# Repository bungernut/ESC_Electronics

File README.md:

# Board
Order the board at oshpark https://oshpark.com/shared_projects/LPLUU39w

# ESC_Electronics
Digikey: https://www.digikey.com/short/nt3pmbw5

|Reference(s)|Value|Digikey|
|-|-|-|
| BT1, BT2, BT3, BT4, BT5, BT6 | 12V | BH23APC-ND |
| C1, C4 | 10uF | 1276-1096-1-ND |
| C2 | open |  |
| C3, C7 | 1nF | 399-CGP1C102KNYDAAWL25-ND |
| C5 | 1pF | 445-180733-1-ND |
| C6 | 4700pF | 399-CGP1C472MNWDAAWL25-ND |
| C8 | open |  |
| C9, C10, C15, C16 | 0.1uF | 1276-1003-1-ND |
| C11, C12 | 330uF | 1189-1766-ND |
| C13, C14 | 0.33uF | 1276-2926-1-ND |
| D1, D2 | RB751V-40 | MBR0540TPMSCT-ND |
| F1, F2 | Polyfuse_Small | 507-1794-1-ND |
| FB1, FB2 | FerriteBead_Small | 732-6715-1-ND |
| H1, H2, H3, H4 | MountingHole |  |
| H5 | DiodeFeedThru |  |
| H6, H7 | MountingHole |  |
| J1 | Batt probe | N/A |
| J2 | CA probe | N/A |
| J3 | Test Input BNC | ARF2005-ND |
| J4 | -1000VDC SHV | 4912-SHV-BR-ND |
| J5 | RV Prob |  |
| J6 | Output BNC | ARF2005-ND |
| J7 | DC Power | WM4825-ND |
| J8 | -8V |  |
| J9 | +8V |  |
| R1 | open |  |
| R2, R3, R5 | 10M | HVA12FA10M0CT-ND |
| R4 | 100M | HVA12FA100MCT-ND |
| R6 | 47 | RPC0805JT47R0 |
| R7 | open |  |
| R8 | 0 | RMCF0805ZT0R00 |
| R9 | 750 | RMCF0805FT750RCT-ND |
| R10 | 20k | RMCF0805FT20K0CT-ND |
| RV1 | 10k | 3266W-103LF-ND |
| U1 | CR110 | ED11161-ND |
| U2 | SiPhotodiode |  |
| U3 | TL051CP | 296-7192-5-ND |
| U4 | UA78M08 | 296-12612-1-ND |
| U5 | UA79M08 | 296-19678-1-ND |

Other items for assembly:
| Part | Ref | Link |
|-|-|-|
| Cremat CR110 | U1 | https://www.cremat.com/home/charge-sensitive-preamplifiers/ |
| SiDiode | U2 | https://www.hamamatsu.com/us/en/product/optical-sensors/photodiodes/si-photodiodes/S3204-09.html |
| 8 PDIP Socket | U3 |  https://www.digikey.com/en/products/detail/te-connectivity-amp-connectors/1-2199298-2/5022039 |
| Red HV Hookup Wire | | https://www.digikey.com/en/products/detail/cnc-tech/3239-24-1-0500-004-1-TS/5968804 |
| BLK HV Hookup Wire | | https://www.digikey.com/en/products/detail/cnc-tech/3239-24-1-0500-001-1-TS/5968800 |
| Electronic Box | | https://www.digikey.com/en/products/detail/bud-industries/CN-5709/1219181 |
| SHV Bulkhead | | https://www.digikey.com/en/products/detail/te-connectivity-amp-connectors/51494-2/298100 |
| Power Cable Assembly | | https://www.digikey.com/en/products/detail/te-connectivity-amp-connectors/2273001-1/5167970 |
| Power Cable Feedthrough | | https://www.digikey.com/en/products/detail/te-connectivity-amp-connectors/T4030014031-000/7927423 |
| Power Supply | | https://www.digikey.com/en/products/detail/xp-power/ECL15UD01-S/4487543 |
| Power Resistors (2x) | | https://www.digikey.com/en/products/detail/ohmite/HS50-100R-J/5307799 |
| AC power feedthrough | | https://www.digikey.com/en/products/detail/davies-molding-llc/GC1000-A/7795436 |

Photo of a completed board:

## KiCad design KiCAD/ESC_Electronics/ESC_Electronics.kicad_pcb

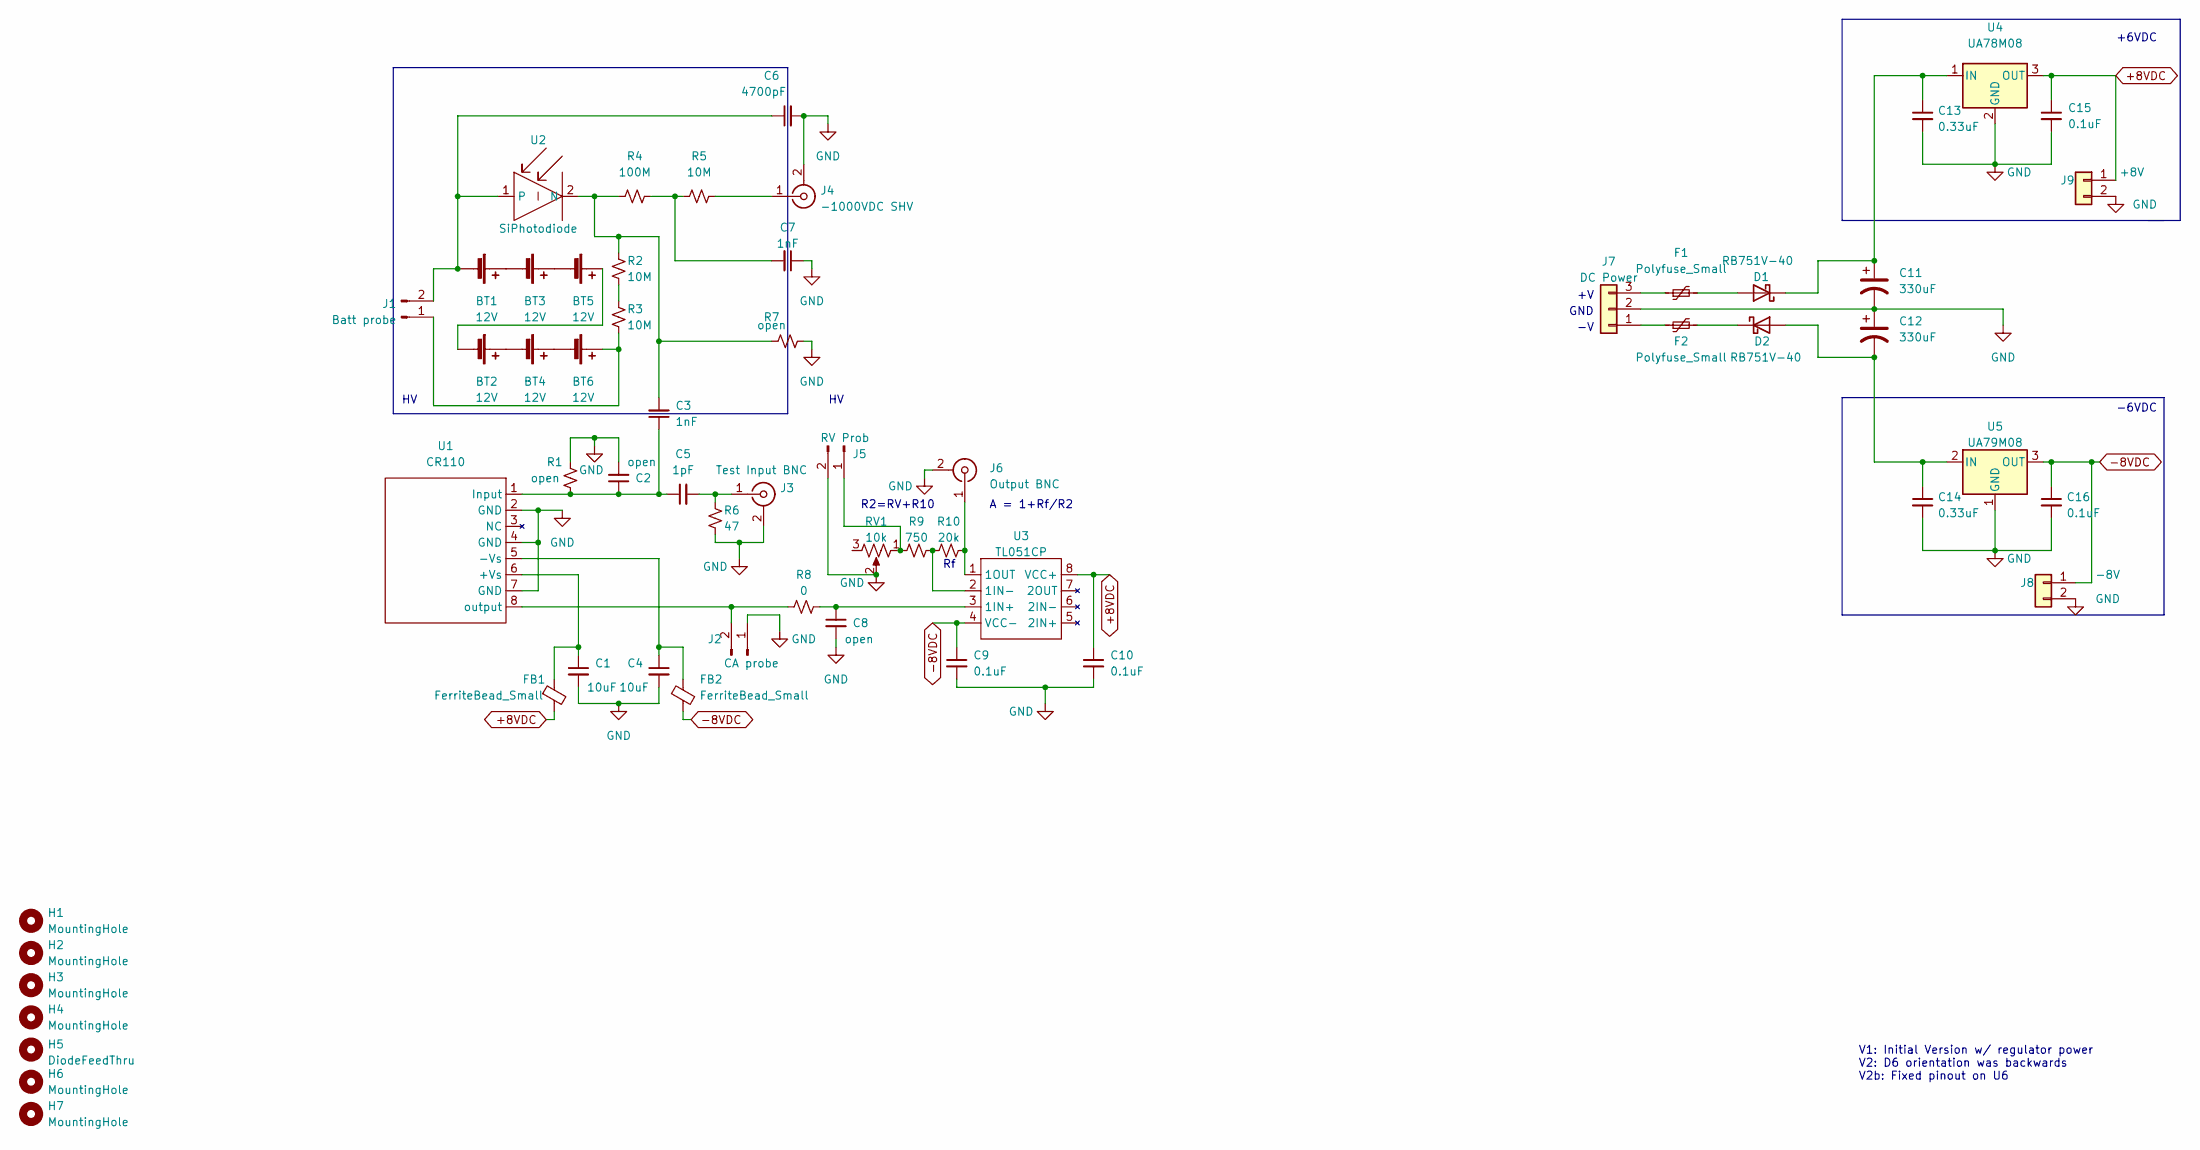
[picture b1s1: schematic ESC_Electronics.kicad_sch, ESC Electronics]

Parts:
BT1, BT2, BT3, BT4, BT5, BT6: 12V; 6S-Battery-Holder; Digikey BH23APC-ND
C1, C4: 10uF; C_0805_2012Metric_Pad1.18x1.45mm_HandSolder; Digikey 1276-1096-1-ND
C2: open; C_Disc_D7.5mm_W5.0mm_P5.00mm
C3, C7: 1nF; C_Disc_D10.5mm_W5.0mm_P10.00mm; Digikey 445-181696-ND
C5: 1pF; C_Disc_D7.5mm_W5.0mm_P5.00mm; Digikey 445-180733-1-ND
C6: 4700pF; C_Disc_D12.5mm_W5.0mm_P10.00mm; Digikey 445-175513-ND
C8: open; C_0805_2012Metric_Pad1.18x1.45mm_HandSolder; Digikey 1276-1096-1-ND
C9, C10: 0.1uF; C_0805_2012Metric_Pad1.18x1.45mm_HandSolder; Digikey 1276-1099-1-ND
C11, C12: 330uF; CP_Radial_D10.0mm_P5.00mm; Digikey 1189-1766-ND
C13, C14: 0.33uF; C_0805_2012Metric_Pad1.18x1.45mm_HandSolder; Digikey 1276-2926-1-ND
C15, C16: 0.1uF; C_0805_2012Metric_Pad1.18x1.45mm_HandSolder; Digikey 1276-2926-1-ND
D1, D2: RB751V-40; D_SOD-123; Digikey MBR0540TPMSCT-ND
F1, F2: Polyfuse_Small; R_1210_3225Metric_Pad1.30x2.65mm_HandSolder; Digikey 507-1794-1-ND
FB1, FB2: FerriteBead_Small; L_1206_3216Metric_Pad1.22x1.90mm_HandSolder; Digikey 732-6715-1-ND
H1, H2, H3, H4: MountingHole; MountingHole_3.2mm_M3
H5: DiodeFeedThru
H6, H7: MountingHole; 4headclear
J1: Batt probe; PinHeader_1x02_P2.54mm_Vertical; Digikey N/A
J2: CA probe; PinHeader_1x02_P2.54mm_Vertical; Digikey N/A
J3: Test Input BNC; BNC_Amphenol_B6252HB-NPP3G-50_Horizontal; Digikey ARF2005-ND
J4: -1000VDC SHV; MHV Wire Conn; Digikey 4912-SHV-BR-ND
J5: RV Prob; PinHeader_1x02_P2.54mm_Vertical
J6: Output BNC; BNC_Amphenol_B6252HB-NPP3G-50_Horizontal; Digikey ARF2005-ND
J7: DC Power; Molex_KK-254_AE-6410-03A_1x03_P2.54mm_Vertical; Digikey WM4825-ND
J8: -8V; PinHeader_1x02_P2.54mm_Vertical
J9: +8V; PinHeader_1x02_P2.54mm_Vertical
R1: open; R_Axial_DIN0207_L6.3mm_D2.5mm_P5.08mm_Vertical
R2, R3: 10M; R_Axial_DIN0207_L6.3mm_D2.5mm_P15.24mm_Horizontal; Digikey HVA12FA10M0CT-ND
R4: 100M; R_Axial_DIN0207_L6.3mm_D2.5mm_P15.24mm_Horizontal; Digikey HVA12FA100MCT-ND
R5: 10M; R_Axial_DIN0207_L6.3mm_D2.5mm_P15.24mm_Horizontal; Digikey HVA12FA10M0
R6: 47; R_0805_2012Metric_Pad1.20x1.40mm_HandSolder; Digikey RPC0805JT47R0
R7: open; R_Axial_DIN0207_L6.3mm_D2.5mm_P15.24mm_Horizontal
R8: 0; R_1206_3216Metric_Pad1.30x1.75mm_HandSolder; Digikey RMCF0805ZT0R00
R9: 750; R_0805_2012Metric_Pad1.20x1.40mm_HandSolder
R10: 20k; R_0805_2012Metric_Pad1.20x1.40mm_HandSolder
RV1: 10k; Potentiometer_Bourns_3266W_Vertical; Digikey 3266W-103LF-ND
U1: CR110; PinHeader_1x08_P2.54mm_Vertical; Digikey ED11161-ND
U2: SiPhotodiode; SolderWire-0.5sqmm_1x02_P4.6mm_D0.9mm_OD2.1mm
U3: TL051CP; DIP-8_W7.62mm_Socket; Digikey 296-7192-5-ND
U4: UA78M08; SOT-223-3_TabPin2; Digikey 296-12612-1-ND
U5: UA79M08; TO-252-3_Tab1; Digikey 296-19678-1-ND

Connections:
+8VDC: C10.1, C15.1, FB1.2, J9.1, U3.8 (VCC+), U4.3 (OUT)
-8VDC: C9.1, C16.1, FB2.2, J8.1, U3.4 (VCC-), U5.3 (OUT)
GND: C1.2, C2.2, C4.2, C6.2, C7.1, C8.2, C9.2, C10.2, C11.2, C12.1, C13.2, C14.2, C15.2, C16.2, J2.1, J3.2 (Ext), J4.2 (Ext), J5.2, J6.2 (Ext), J7.2, J8.2, J9.2, R1.2, R6.2, R7.2, RV1.2, U1.2 (GND), U1.4 (GND), U1.7 (GND), U4.2 (GND), U5.1 (GND)
unnamed: BT1.1 (+), BT3.2 (-)
unnamed: BT1.2 (-), C6.1, J1.2, U2.1
unnamed: BT2.1 (+), BT4.2 (-)
unnamed: BT2.2 (-), BT5.1 (+)
unnamed: BT3.1 (+), BT5.2 (-)
unnamed: BT4.1 (+), BT6.2 (-)
unnamed: BT6.1 (+), J1.1, R3.1
unnamed: C7.2, R4.2, R5.1
unnamed: D1.2 (A), F1.2
unnamed: C11.1, C13.1, D1.1 (K), U4.1 (IN)
unnamed: C12.2, C14.1, D2.2 (A), U5.2 (IN)
unnamed: D2.1 (K), F2.2
unnamed: J2.2, R8.1, U1.8 (output)
unnamed: C5.2, J3.1 (In), R6.1
unnamed: J4.1 (In), R5.2
unnamed: J5.1, R9.1, RV1.1
unnamed: J6.1 (In), R10.2, U3.1 (1OUT)
unnamed: F2.1, J7.1
unnamed: F1.1, J7.3
unnamed: R2.1, R3.2
unnamed: C1.1, FB1.1, U1.6 (+Vs)
unnamed: C4.1, FB2.1, U1.5 (-Vs)
unnamed: C2.1, C3.1, C5.1, R1.1, U1.1 (Input)
unnamed: C3.2, R2.2, R4.1, R7.1, U2.2 (N)
unnamed: C8.1, R8.2, U3.3 (1IN+)
unnamed: R9.2, R10.1, U3.2 (1IN-)

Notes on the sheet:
+6VDC
-6VDC
GND
V1: Initial Version w/ regulator power V2: D6 orientation was backwards V2b: Fixed pinout on U6
R2=RV+R10
A = 1+Rf/R2

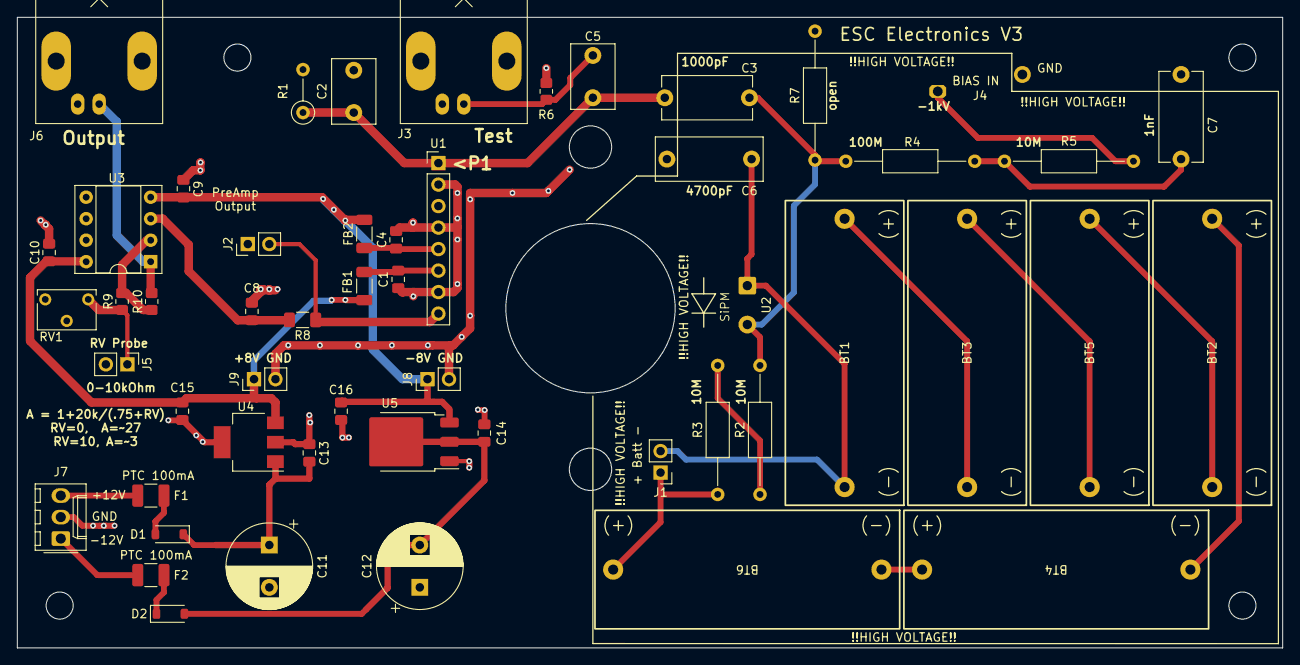
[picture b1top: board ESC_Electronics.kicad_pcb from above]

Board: 2 copper layers, 149.5 x 74.5 mm, 60 parts (0 on the bottom side), 29 nets.

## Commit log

2022-08-17 laying out V1
2022-08-17 layed out board
2022-08-19 uploaded this version to OSHpark as V1
2022-08-19 the real ESC V1
2022-10-11 Refining for V2 while debugging
2022-10-11 Refining for V2 while debugging R2
2022-10-11 Refining for V2 while debugging R3
2022-10-17 Refining for V2 while debugging R4
2022-10-18 Update README.md
    Updates for R2
2022-11-09 published as V2 on OSHPark
2023-06-30 fixed U6 pad and updated several footprints to latest KiCAD versions
2023-06-30 Updated PDB label to V2b for #4 fix
2023-07-06 Updating Digikey Partnumbers
2023-07-06 Cleaning up SCH w/ notes
2023-08-08 Another mistake on the Neg8V resistor
2023-09-27 Modification for external PS
2023-10-12 Updating docs
2023-10-13 added PTC to power input
2023-10-13 Updating Readme
2025-02-11 Update README.md
    added photo of a completed board
